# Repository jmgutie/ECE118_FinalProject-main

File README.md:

# ECE118 FinalProject Soccer Droid

## Name
Mech Final Project -- The M.E Complexity --

## Description
The objective is to construct a small independent robot that can navigate a standardized field with efficiency and robustness, locate the goal location, and shoot the ping-pong ball into the goal. Points will be awarded for each ball that makes it into the goal, and additional points will be given for more difficult zones on the field. 

## Visuals

## Authors and acknowledgment
Jose Mario Gutierrez
Eliot Wachtel

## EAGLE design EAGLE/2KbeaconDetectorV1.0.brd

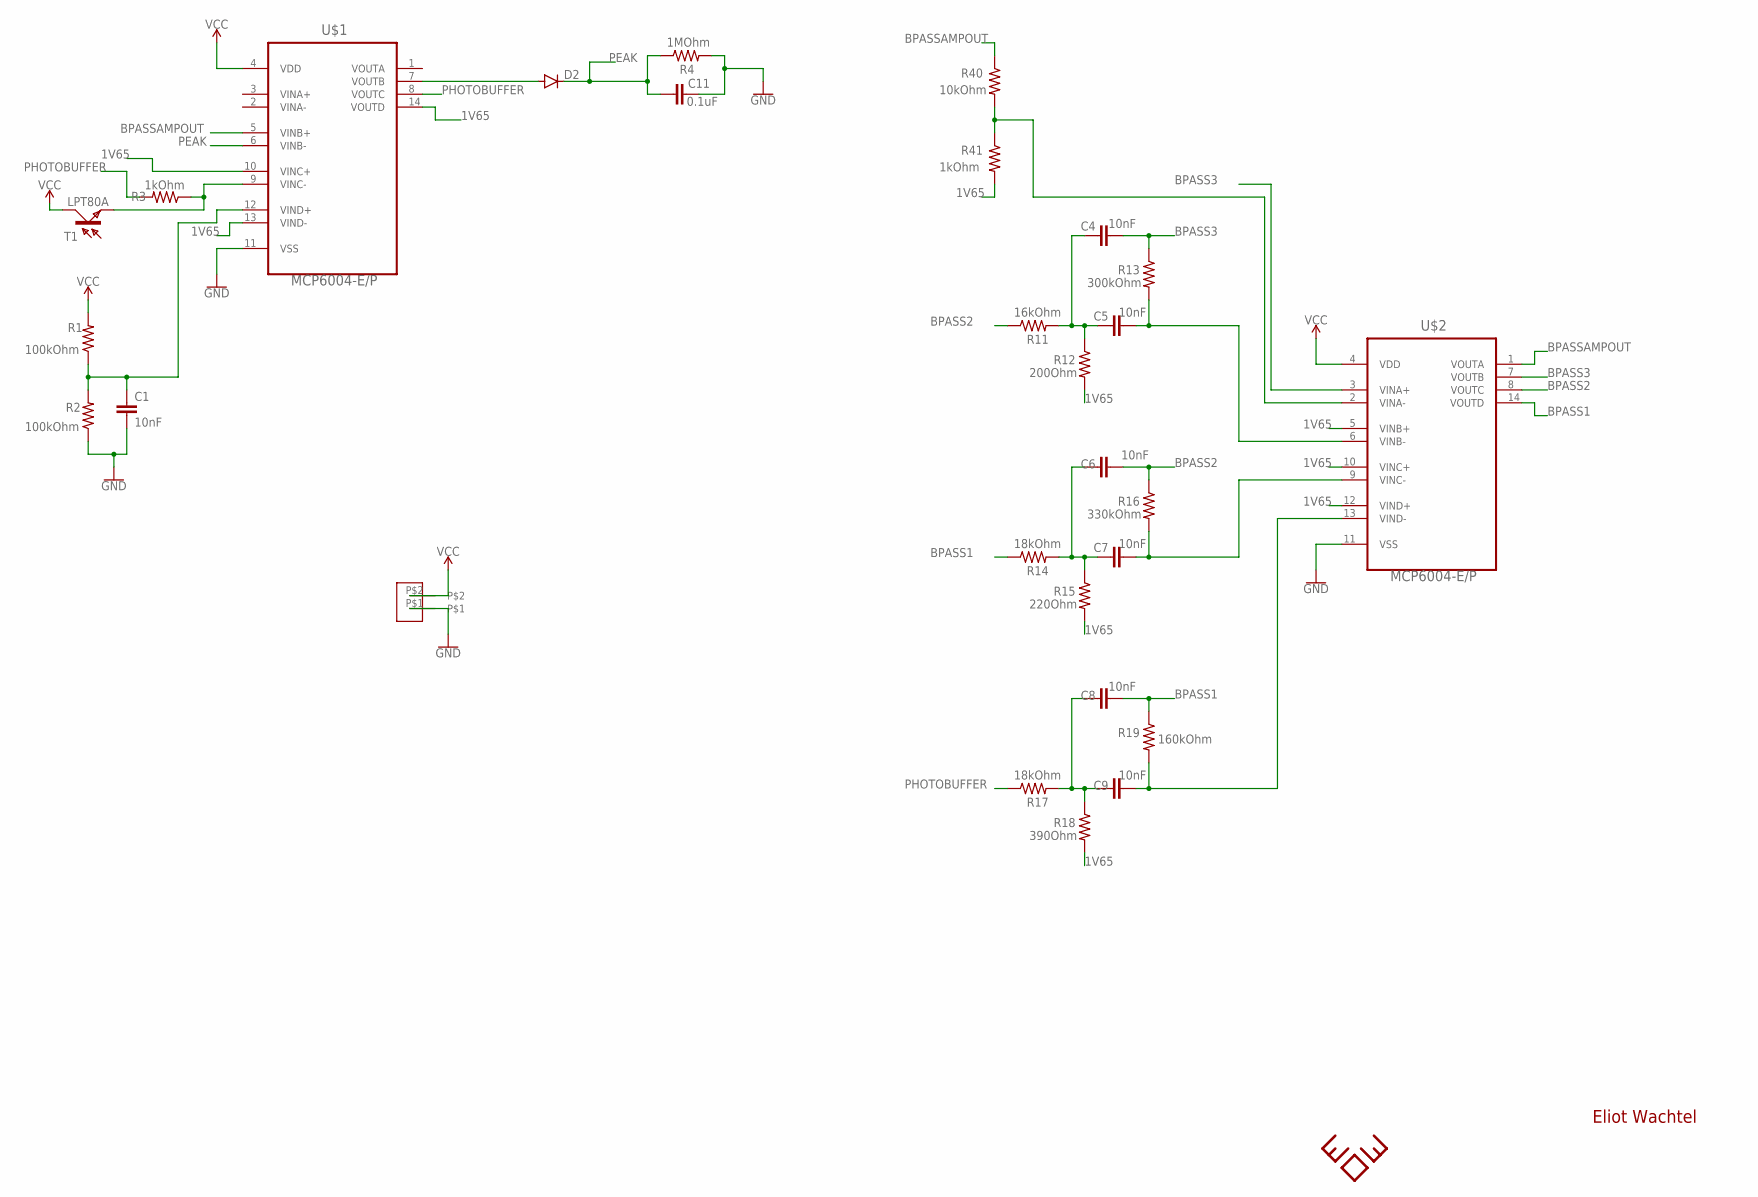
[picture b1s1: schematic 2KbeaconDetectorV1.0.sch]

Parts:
C1, C4, C5, C6, C7, C8, C9: 10nF; C5B2.5
C11: 0.1uF; C5B2.5
D2: DIODE-D-7.5; D-7.5
R1, R2: 100kOhm; 0207/5V
R3: 1kOhm; 0204V
R4: 1MOhm; 0204/5
R11: 16kOhm; 0204V
R12: 200Ohm; 0204/7
R13: 300kOhm; 0204V
R14, R17: 18kOhm; 0204V
R15: 220Ohm; 0204/7
R16: 330kOhm; 0204V
R18: 390Ohm; 0204/7
R19: 160kOhm; 0204V
R40: 10kOhm; 0204/7
R41: 1kOhm; 0204/7
T1: LPT80A
U$1, U$2: MCP6004-E/P; DIP254P762X533-14
U$4: WIRECONNECT2PIN

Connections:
1V65: R12.2, R15.2, R18.2, R41.2, U$1.10 (VINC+), U$1.13 (VIND-), U$1.14 (VOUTD), U$2.5 (VINB+), U$2.10 (VINC+), U$2.12 (VIND+)
BPASS1: C8.2, R14.1, R19.1, U$2.14 (VOUTD)
BPASS2: C6.2, R11.1, R16.1, U$2.8 (VOUTC)
BPASS3: C4.2, R13.1, U$2.3 (VINA+), U$2.7 (VOUTB)
BPASSAMPOUT: R40.1, U$1.5 (VINB+), U$2.1 (VOUTA)
GND: C1.2, C11.2, R2.1, R4.2, U$1.11 (VSS), U$2.11 (VSS), U$4.P$1
unnamed: C1.1, R1.1, R2.2, U$1.12 (VIND+)
unnamed: D2.A, U$1.7 (VOUTB)
unnamed: R3.1, T1.E, U$1.9 (VINC-)
unnamed: C4.1, C5.1, R11.2, R12.1
unnamed: C7.2, R16.2, U$2.9 (VINC-)
unnamed: C6.1, C7.1, R14.2, R15.1
unnamed: C9.2, R19.2, U$2.13 (VIND-)
unnamed: C8.1, C9.1, R17.2, R18.1
unnamed: C5.2, R13.2, U$2.6 (VINB-)
unnamed: R40.2, R41.1, U$2.2 (VINA-)
PEAK: C11.1, D2.C, R4.1, U$1.6 (VINB-)
PHOTOBUFFER: R3.2, R17.1, U$1.8 (VOUTC)
VCC: R1.2, T1.C, U$1.4 (VDD), U$2.4 (VDD), U$4.P$2

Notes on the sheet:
Eliot Wachtel

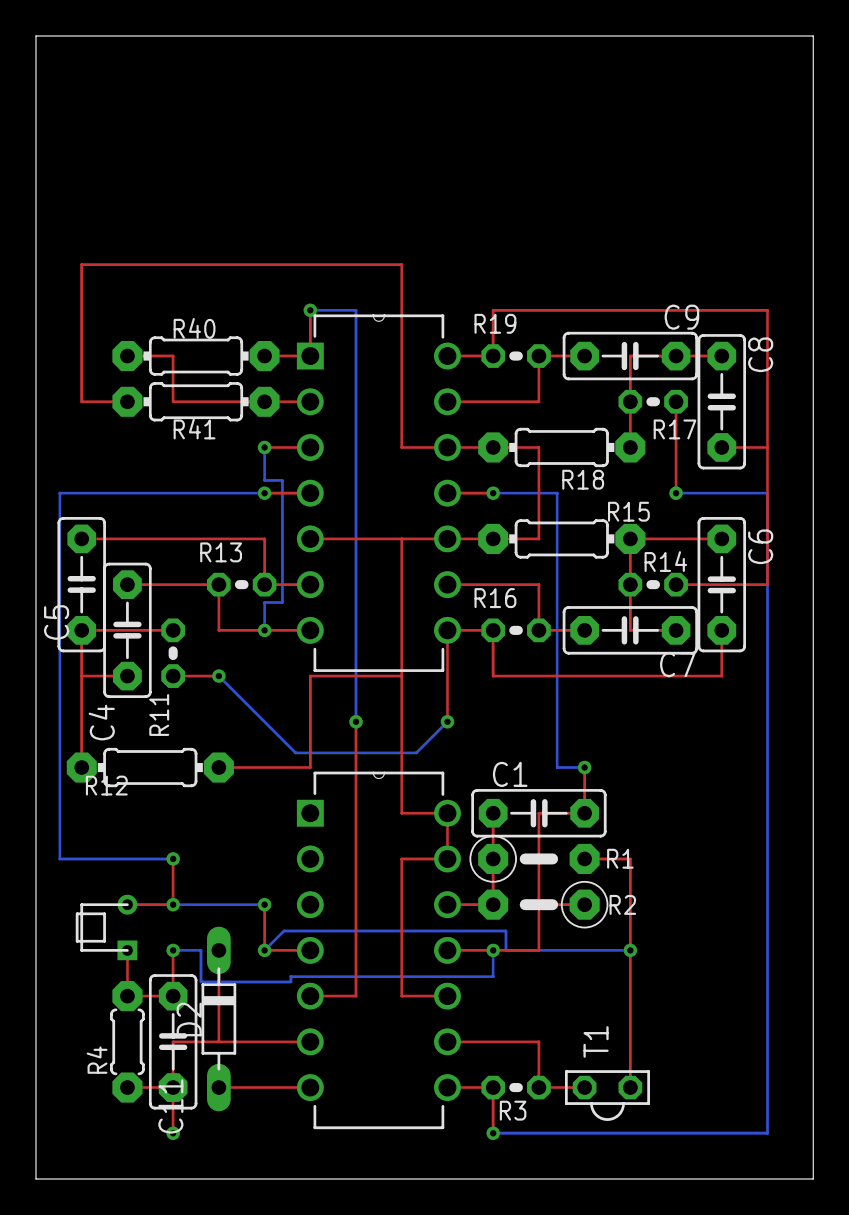
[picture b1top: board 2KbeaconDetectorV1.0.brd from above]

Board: 2 copper layers, 43.2 x 63.5 mm, 28 parts (0 on the bottom side), 19 nets.

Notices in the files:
parts and their libraries:
SparkFun-PowerSymbols: Licensing: Creative Commons ShareAlike 4.0 International - https://creativecommons.org/licenses/by-sa/4.0
